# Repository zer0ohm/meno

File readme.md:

# meno
試作中のArduino互換機 (無保証)

## Meno
マイコンにATmega2560、USBコネクタにType-Cを採用したボードです。 GPIOは公式のMEGAと同じ70本です。(内訳: ディジタルI/O 54本、アナログI/O 16本)
* 回路図: [Meno_sch.pdf](https://github.com/zer0ohm/meno/blob/master/Meno/Schematic/Meno_sch.pdf)
* 部品表: [Meno_BOM.pdf](https://github.com/zer0ohm/meno/blob/master/Meno/Docs/Meno_BOM.pdf) もしくは [Meno_BOM.md](https://github.com/zer0ohm/meno/blob/master/Meno/Docs/Meno_BOM.md)
* 組み立て方法: [Meno_assemble.md](https://github.com/zer0ohm/meno/blob/master/Meno/Docs/Meno_assemble.md)

<!--// まだ構想中なのでとりあえずコメントアウト
## Meno F4
MenoのマイコンをSTM32F4(STM32F446RET)にアップグレードしたボードです。USBコネクタは引き続きType-Cを採用しています。
* 回路図: [MenoF4_RevPrototype_sch.pdf](https://github.com/zer0ohm/meno/blob/master/MenoF4/Schematic/MenoF4_RevPrototype_sch.pdf)
* 部品表: [MenoF4_BOM.pdf](https://github.com/zer0ohm/meno/blob/master/MenoF4/Docs/MenoF4_BOM.pdf) もしくは [MenoF4_BOM.md](https://github.com/zer0ohm/meno/blob/master/MenoF4/Docs/MenoF4_BOM.md)
* 組み立て方法: [MenoF4_assemble.md](https://github.com/zer0ohm/meno/blob/master/MenoF4/Docs/Meno_assemble.md)
-->

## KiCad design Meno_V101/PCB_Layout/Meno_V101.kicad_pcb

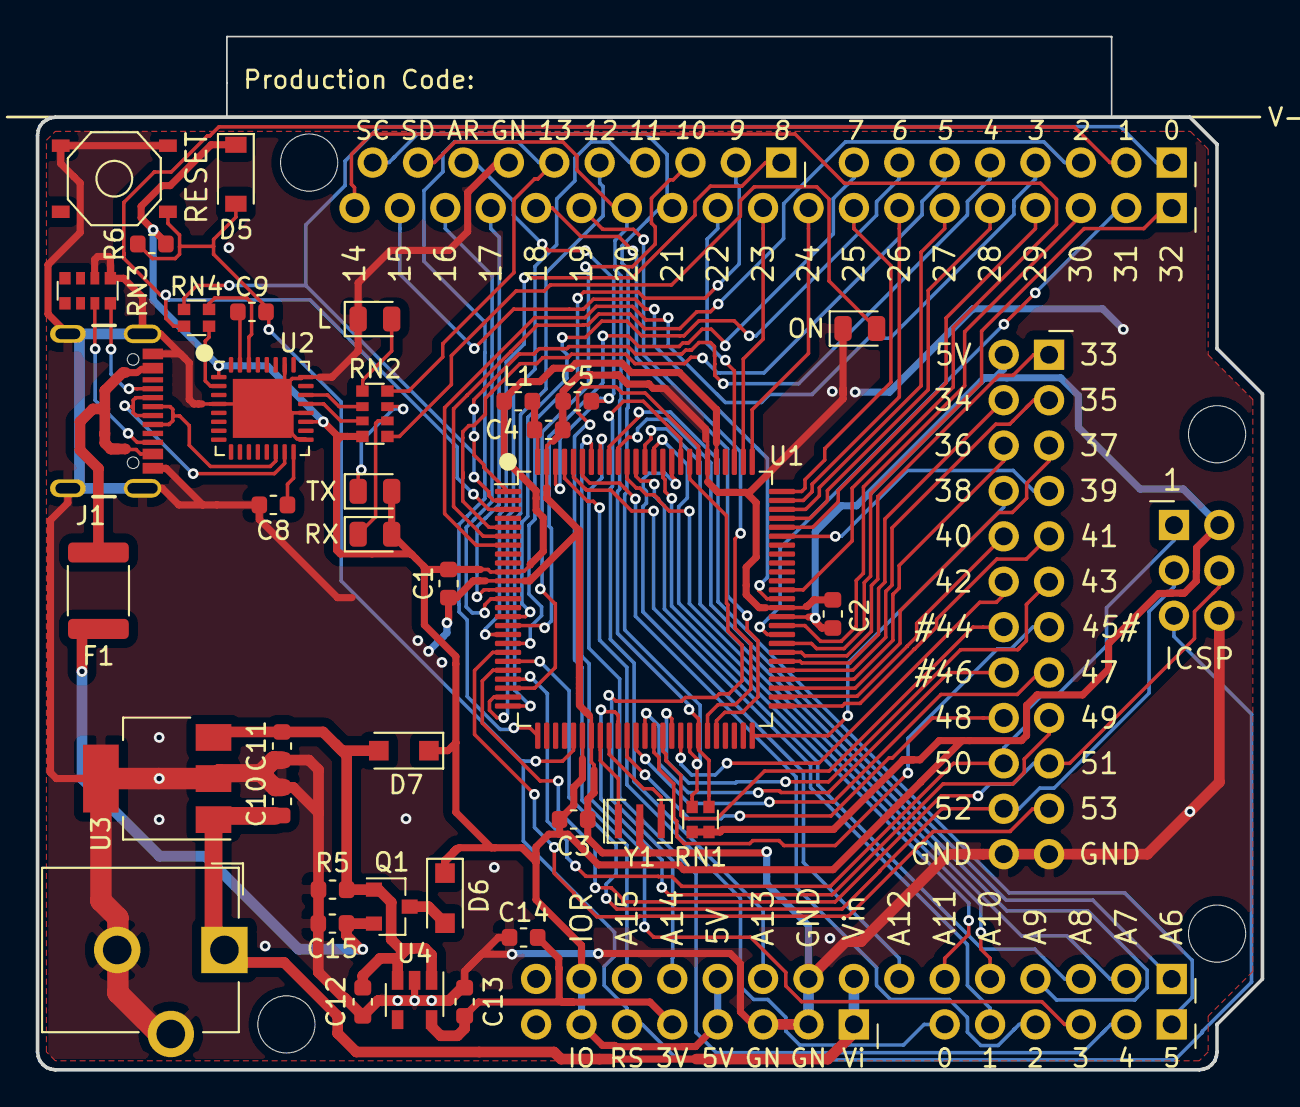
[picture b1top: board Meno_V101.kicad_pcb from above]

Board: 2 copper layers, 68.5 x 57.8 mm, 50 parts (1 on the bottom side), 97 nets.

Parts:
C1, C2, C3, C4, C5, C8, C9, C11, C14: 0.1u; C_0603_1608Metric
C10: 0.22u; C_0603_1608Metric
C12, C13, C15: 1u; C_0603_1608Metric
D1, D2, D3, D4: PG1112H-TR; LED_0805_2012Metric
D5: 1N4148W; D_SOD-123
D6, D7: RB160MM-30; D_SOD-123F
F1: MF-MSMF050-2; Fuse_1812_4532Metric
J1: 5077CR-16SMC2; GCT_USB4105-GF-A
J2: AVR-ISP-6; PinHeader_2x03_P2.54mm_Vertical
J3: 18742; BarrelJack_CUI_PJ-102AH_Horizontal
J4, J8: Conn_01x08; PinSocket_1x08_P2.54mm_Vertical
J5: Conn_01x10; PinSocket_1x10_P2.54mm_Vertical
J6: Conn_01x19; PinSocket_1x19_P2.54mm_Vertical
J7: Conn_01x06; PinSocket_1x06_P2.54mm_Vertical
J9: Conn_01x15; PinSocket_1x15_P2.54mm_Vertical
J10: Conn_02x12; PinSocket_2x12_P2.54mm_Vertical
L1: BLM18KG300JH1D; L_0603_1608Metric
MH1, MH2, MH3, MH4: Mount_TH_3.2mm_NoWasher
Q1: IRLML6402; SOT-23
R5, R6: 10k; R_0603_1608Metric
RN1: 10k; R_Array_Convex_2x0606
RN2: 1k; R_Array_Convex_4x0612
RN3: 5.1k; R_Array_Convex_4x0612
RN4: 1k; R_Array_Convex_2x0606
SW1: PTS526 SM15 SMTR2 LFS; PTS526_SM15_SMTR2_LFS
U1: ATmega2560-16AUR; TQFP-100_14x14mm_P0.5mm
U2: FT232RQ; QFN-32-1EP_5x5mm_P0.5mm_EP3.3x3.3mm
U3: LM340MPX-5.0/NOPB; SOT-223-3_TabPin2
U4: TLV75733PDBVR; SOT-23-5
Y1: CSTNE16M0V530000R0; Resonator_SMD_muRata_CSTxExxV-3Pin_3.0x1.1mm
ZLS1: Amateur Intent Logo (Designed by @MakoTr_01); amateur_intent_820dpi

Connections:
+3V3: C13.1, C14.1, J8.5, U4.5
+5V: C1.1, C2.1, C3.1, D2.2, D3.2, D5.1, D6.1, D7.1, J2.2, J8.4, J8.7, J9.11, J9.14, J10.2, L1.2, R6.1, RN1.3, RN1.4, RN2.4, U1.10, U1.31, U1.61, U1.80, U2.1, U2.19
/USB_Regulator_Other/D+: J1.A6, J1.B6, U2.14
/USB_Regulator_Other/D-: J1.A7, J1.B7, U2.15
/USB_Regulator_Other/RXLED: RN2.3, U2.21
/USB_Regulator_Other/TXLED: RN2.2, U2.22
A0: J7.6, U1.97
A1: J7.5, U1.96
A2: J7.4, U1.95
A3: J7.3, U1.94
A4: J7.2, U1.93
A5: J7.1, U1.92
A6: J9.1, U1.91
A7: J9.2, U1.90
A8: J9.3, U1.89
A9: J9.4, U1.88
A10: J9.5, U1.87
A11: J9.6, U1.86
A12: J9.7, U1.85
A13: J9.10, U1.84
A14: J9.12, U1.83
A15: J9.13, U1.82
AREF: C5.1, J5.8, U1.98
D0: J4.1, RN4.1, U1.2
D1: J4.2, RN4.2, U1.3
D2: J4.3, U1.6
D3: J4.4, U1.7
D4: J4.5, U1.1
D5: J4.6, U1.5
D6: J4.7, U1.15
D7: J4.8, U1.16
D8: J5.1, U1.17
D9: J5.2, U1.18
D10: J5.3, U1.23
D11: J5.4, U1.24
D12: J5.5, U1.25
D13: J5.6, RN2.8, U1.26
D14: J6.19, U1.64
D15: J6.18, U1.63
D16: J6.17, U1.13
D17: J6.16, U1.12
D18: J6.15, U1.46
D19: J6.14, U1.45
D20: J5.9, J6.13, RN1.1, U1.44
D21: J5.10, J6.12, RN1.2, U1.43
D22: J6.11, U1.78
D23: J6.10, U1.77
D24: J6.9, U1.76
D25: J6.8, U1.75
D26: J6.7, U1.74
D27: J6.6, U1.73
D28: J6.5, U1.72
D29: J6.4, U1.71
D30: J6.3, U1.60
D31: J6.2, U1.59
D32: J6.1, U1.58
D33: J10.1, U1.57
D34: J10.4, U1.56
D35: J10.3, U1.55
D36: J10.6, U1.54
D37: J10.5, U1.53
D38: J10.8, U1.50
D39: J10.7, U1.70
D40: J10.10, U1.52
D41: J10.9, U1.51
D42: J10.12, U1.42
D43: J10.11, U1.41
D44: J10.14, U1.40
D45: J10.13, U1.39
D46: J10.16, U1.38
D47: J10.15, U1.37
D48: J10.18, U1.36
D49: J10.17, U1.35
D50: J2.1, J10.20, U1.22
D51: J2.4, J10.19, U1.21
D52: J2.3, J10.22, U1.20
D53: J10.21, U1.19
GND: C1.2, C2.2, C3.2, C4.2, C5.2, C8.2, C10.2, C11.2, C12.2, C13.2, C14.2, C15.2, D1.1, D4.1, J1.A1/B12, J1.B1/A12, J1.G1, J1.G2, J1.G3, J1.G4, J2.6, J3.2, J3.3, J5.7, J8.2, J8.3, J9.9, J10.23, J10.24, R5.2, RN3.1, RN3.2, SW1.1, SW1.2, U1.11, U1.32, U1.62, U1.81, U1.99, U2.4, U2.17, U2.20, U2.24, U2.26, U2.33, U3.2, U4.2, Y1.2
unnamed: C4.1, L1.1, U1.100
unnamed: C8.1, U2.16
unnamed: C9.2, U2.31
unnamed: C11.1, C12.1, D7.2, Q1.1, R5.1, U3.3, U4.1, U4.3
unnamed: C15.1, F1.1, Q1.2
unnamed: D1.2, RN2.1
unnamed: D2.1, RN2.7
unnamed: D3.1, RN2.6
unnamed: D4.2, RN2.5
unnamed: D6.2, Q1.3
unnamed: J1.A5, RN3.8
unnamed: J1.B5, RN3.7
unnamed: RN4.3, U2.2
unnamed: RN4.4, U2.30
unnamed: U1.33, Y1.1
unnamed: U1.34, Y1.3
RST: C9.1, D5.2, J2.5, J8.6, R6.2, SW1.4, U1.30
VBUS: F1.2, J1.A4/B9, J1.B4/A9
VS: C10.1, J3.1, J8.1, J9.8, U3.1

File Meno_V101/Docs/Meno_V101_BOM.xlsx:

Meno Ver. 1.01 部品表(Bills of materials) v1.0-20200801ブヒンヒョウ
部品指示番号ブヒンシジバンゴウ | 個数コスウ | 定数等テイスウトウ | 製造元型番セイゾウゲンカタバン | 製造元セイゾウゲン | 部品概要ブヒンガイヨウ
C1,2,3,4,5,8,9,11,14 | 9 | 0.1uF | UMK107B7104KA-T | Taiyo Yuden | バイパスコンデンサ
C10 | 1 | 0.33uF | CGA3E3X7R1H334K080AB | TDK | 5Vレギュレータ用入力コンデンサヨウニュウリョク
C12,13,15 | 3 | 1uF | UMK107AB7105KA-T | Taiyo Yuden | バイパスコンデンサ
D1,2,3,4 | 4 | PG1112H-TR | PG1112H-TR | Stanley Electric | インジケータ用LEDヨウ
D5 | 1 | 1N4148W | 1N4148W-13-F | Diodes Incorporated | 逆流防止ダイオードギャクリュウボウ
D6,7 | 2 | RB160MM-30 | RB160MM-30TR | Rohm Semiconductor | ショットキーダイオード
F1 | 1 | MF-MSMF050-2 | MF-MSMF050-2 | Bourns | ポリヒューズ
J1 | 1 | 5077CR-16SMC2 | USB4105-GF-A | GCT | USB Type-Cレセプタクル
J2 | 1 | AVR-ISP-6 | M20-9980345 (*1) | Harwin | AVR用6ピンICSPヨウ
J3 | 1 | 18742 | PJ-102A | CUI Devices | DCジャック
J4,8 | 2 | Conn_01x08 | PPTC081LFBN-RC (*1) | Sullins Connector Solutions | マイコン入出力/電源用ピンソケットデンゲン
J5 | 1 | Conn_01x10 | PPTC101LFBN-RC (*1) | Sullins Connector Solutions | マイコン入出力用ピンソケットニュウシュツヨウ
J6 | 1 | Conn_01x19 | PPTC191LFBN-RC (*1) | Sullins Connector Solutions | マイコン入出力用ピンソケットニュウシュツヨウ
J7 | 1 | Conn_01x06 | PPTC061LFBN-RC (*1) | Sullins Connector Solutions | マイコン入出力用ピンソケットニュウシュツヨウ
J9 | 1 | Conn_01x15 | PPTC151LFBN-RC (*1) | Sullins Connector Solutions | マイコン入出力用ピンソケットニュウシュツヨウ
J10 | 1 | Conn_02x12 | PPTC122LFBN-RC (*1) | Sullins Connector Solutions | マイコン入出力用ピンソケットニュウシュツヨウ
L1 | 1 | BLM18KG300JH1D | BLM18KG300JH1D | Murata Electronics | マイコンのAVCC用LCフィルタの"L"側ガワ
Q1 | 1 | IRLML6402 | IRLML6402TRPBF | Infineon Technologies | 電源切替用PMOSデンゲンキリカエヨウ
RN1 | 1 | 10kΩ | EXB-38V103JV | Panasonic | プルアップ抵抗テイコウ
RN2 | 1 | 1kΩ | EXB-38V102JV | Panasonic | LED保護抵抗ホゴテイコウ
RN3 | 1 | 5.1kΩ | CAY16-512J4LF (*2) | Bourns | USB Type-C CCプルダウン抵抗
RN4 | 1 | 1kΩ | EXB-34V102JV | Panasonic | UART抵抗テイコウ
R5,6 | 2 | 10kΩ | RK73B1JTTD103J | KOA | プルアップ/ダウン抵抗
SW1 | 1 | PTS526-SM15 | PTS526 SM15 SMTR2 LFS | C&K | タクタイルスイッチ
U1 | 1 | ATmega2560-16AUR | ATmega2560-16AUR | Atmel | マイコン
U2 | 1 | FT232RQ | FT232RQ-REEL | FTDI | USB/UART変換ICヘンカン
U3 | 1 | LM340MPX-5.0/NOPB | LM340MPX-5.0/NOPB | Texas Instruments | 5Vレギュレータ
U4 | 1 | TLV75733PDBVR | TLV75733PDBVR | Texas Instruments | 3.3Vレギュレータ
Y1 | 1 | CSTNE16M0V530000R0 | CSTNE16M0V530000R0 | Murata Electronics | セラミック発振子
*1: ピンソケット/ヘッダはロットによって変更あり
*2: 入手困難な為急遽変更 EXB-34V512JV → CAY16-512J4LF
*3: *2での変更に伴いフットプリントを変更 Convex_2x0606 → Convex_4x0612

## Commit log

2020-03-17 回路図データを追加
2020-03-17 CCライセンスのファイルを追加
2020-03-17 部品表等を追加
2020-03-17 回路図内のURLを修正
2020-03-17 README内にURLを追加
2020-03-18 BOMのバージョン名を修正
2020-03-18 ルートリポジトリのREADMEを更新
2020-03-19 基板の設計データを追加
2020-03-19 基板のガーバーデータを追加
2020-03-19 メタルマスクのガーバーデータを追加
2020-03-19 fix filename typo
2020-03-19 URLを修正
2020-03-19 部品表のフットプリントを修正
2020-03-20 ピンヘッダ/ソケットの位置を修正
2020-03-20 シルクを修正
2020-03-20 cad32c7での修正に合わせてガーバーデータを更新
2020-03-23 インデントを修正
2020-03-27 ピンソケットの構成を変更
2020-03-27 0ecd643での変更を基板データに反映
2020-03-27 add6f1aで反映したデータをガーバー化
2020-03-27 0ecd643での変更を部品表に反映
2020-03-27 ピン配置図を更新
2020-06-07 update images
2020-08-01 Meno Ver1.01 first commit
2020-08-02 シルクと一部配線の調整
2020-08-08 プリント基板のパターンとシルク位置の変更
